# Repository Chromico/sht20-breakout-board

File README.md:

# SHT20 breakout board
An open source temperature and humidity sensor breakout board based on the SHT20 sensor from Sensirion. The board is only 10x10mm making it ideal for compact spaces/projects that need a decent temperature and humidity sensor. 

My website: https://tecknologg.website

# Front 

# Back

# SHT20 breakout board next to a 20 Mauritian cent coin

# Documentation

You can get the official documentation here: https://github.com/Chromico/sht20-breakout-board/blob/main/documentation/SHT20%20Temperature%20and%20Humidity%20Sensor%20Breakout%20Board%20Documentation.pdf

# Certification

# Contact

Need to contact me ? Just send me an email at nathan@tecknologg.website or tecknologg@gmail.com

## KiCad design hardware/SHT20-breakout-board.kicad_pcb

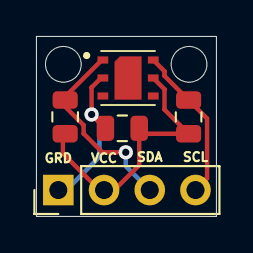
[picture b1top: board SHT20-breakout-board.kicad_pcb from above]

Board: 2 copper layers, 10.0 x 10.0 mm, 5 parts (0 on the bottom side), 5 nets.

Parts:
C1: C; C_0805_2012Metric
J1: Breakout pins; PinHeader_1x04_P2.54mm_Vertical
R1, R2: R; C_0805_2012Metric
U1: SHT20; XDCR_SHT20

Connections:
+3V3: C1.1, J1.2, R1.1, R2.2, U1.5
/SCL: J1.4, R1.2, U1.6
/SDA: J1.3, R2.1, U1.1
GND: C1.2, J1.1, U1.2
unnamed: U1.3, U1.4

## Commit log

2020-10-11 Hardware files and gerbers added to repo
2020-10-11 Add the images from github GUI
2020-10-11 Add the banner
2020-10-11 lorem ipsum
2020-10-15 Make a better doc template one day :P
2020-10-15 the banner
2020-10-15 Create LICENSE
2020-10-17 open hardware certification logo added
2020-10-17 [ImgBot] Optimize images
    *Total -- 2,154.07kb -> 2,022.00kb (6.13%)
    /images/banner.png -- 418.30kb -> 368.50kb (11.91%)
    /images/board_coin.jpg -- 585.31kb -> 556.17kb (4.98%)
    /images/front.jpg -- 608.05kb -> 578.52kb (4.86%)
    /images/back.jpg -- 542.41kb -> 518.81kb (4.35%)
